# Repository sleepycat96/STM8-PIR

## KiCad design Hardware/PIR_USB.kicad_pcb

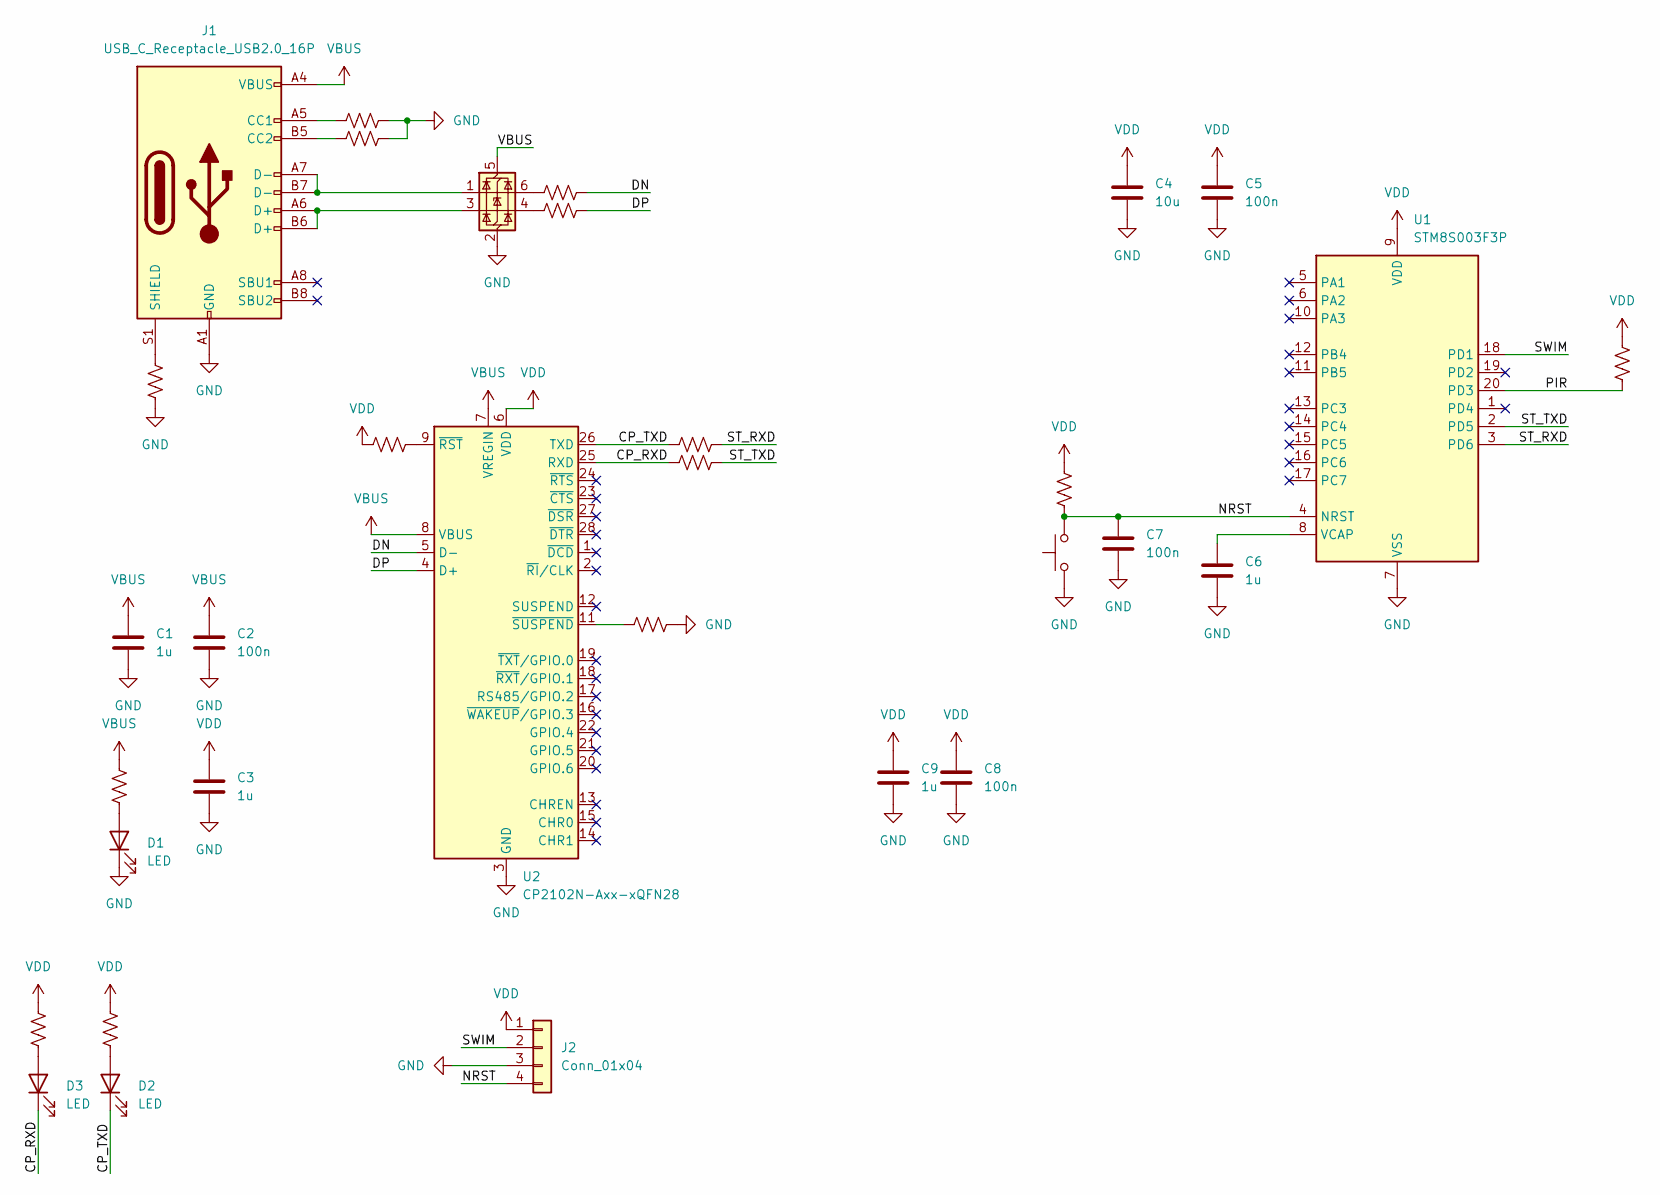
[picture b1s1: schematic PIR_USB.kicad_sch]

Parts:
C1, C3, C6, C9: 1u; C_0603_1608Metric
C2, C5, C7, C8: 100n; C_0603_1608Metric
C4: 10u; CP_EIA-3216-10_Kemet-I
D1, D2, D3: LED; LED_0603_1608Metric
J1: USB_C_Receptacle_USB2.0_16P; USB_C_Receptacle_GCT_USB4105-xx-A_16P_TopMnt_Horizontal
J2: Conn_01x04
R1, R2: 5.1k; R_0603_1608Metric
R3, R4, R7, R8: 22R; R_0603_1608Metric
R5, R9, R10, R11, R12, R13, R14: 10k; R_0603_1608Metric
R6: 0R; R_0603_1608Metric
SW1: SW_Push
U1: STM8S003F3P; TSSOP-20_4.4x6.5mm_P0.65mm
U2: CP2102N-Axx-xQFN28; QFN-28-1EP_5x5mm_P0.5mm_EP3.35x3.35mm
U3: USBLC6-2SC6; SOT-23-6

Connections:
/CP_RXD: D3.1 (K), R8.1, U2.25 (RXD)
/CP_TXD: D2.1 (K), R7.1, U2.26 (TXD)
/DN: R3.2, U2.5 (D-)
/DP: R4.2, U2.4 (D+)
/NRST: C7.1, J2.4, R13.1, SW1.2, U1.4 (NRST)
/ONTIME: U1.1 (PD4); also elsewhere on the board
/PIR: R14.1, U1.20 (PD3); also elsewhere on the board
/ST_RXD: R7.2, U1.3 (PD6)
/ST_TXD: R8.2, U1.2 (PD5)
/SWIM: J2.2, U1.18 (PD1)
GND: C1.2, C2.2, C3.2, C4.2, C5.2, C6.2, C7.2, C8.2, C9.2, D1.1 (K), J1.A1 (GND), J1.A12 (GND), J1.B1 (GND), J1.B12 (GND), J1.S1 (SHIELD), J2.3, R1.2, R2.2, R6.1, R6.2, R9.2, SW1.1, U1.7 (VSS), U2.3 (GND), U2.29 (GND), U3.2 (GND); also elsewhere on the board
unnamed: D1.2 (A), R10.1
unnamed: D2.2 (A), R11.1
unnamed: D3.2 (A), R12.1
unnamed: J1.A5 (CC1), R2.1
unnamed: J1.B5 (CC2), R1.1
unnamed: J1.A6 (D+), J1.B6 (D+), U3.3 (I/O2)
unnamed: J1.A7 (D-), J1.B7 (D-), U3.1 (I/O1)
unnamed: R3.1, U3.6 (I/O1)
unnamed: R4.1, U3.4 (I/O2)
unnamed 21: U1.5 (PA1); also elsewhere on the board
unnamed: C6.1, U1.8 (VCAP)
unnamed: R5.2, U2.9 (~RST)
unnamed: R9.1, U2.11 (~SUSPEND)
VBUS: C1.1, C2.1, J1.A4 (VBUS), J1.A9 (VBUS), J1.B4 (VBUS), J1.B9 (VBUS), R10.2, U2.7 (VREGIN), U2.8 (VBUS), U3.5 (VBUS)

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
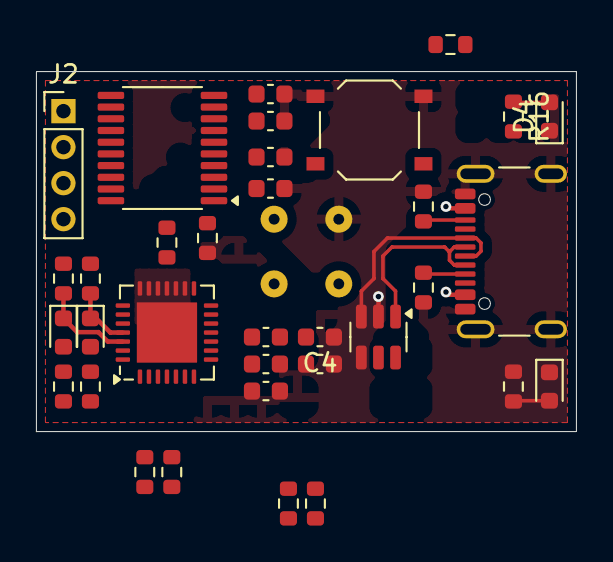
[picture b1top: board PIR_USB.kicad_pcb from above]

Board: 2 copper layers, 30.0 x 20.0 mm, 35 parts (1 on the bottom side), 27 nets.

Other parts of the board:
D4: LED; LED_0603_1608Metric
J3: BS412
R15, R16: 10k; R_0603_1608Metric

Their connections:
/ONTIME: J3.2, R15.1; also elsewhere on the board
/PIR: J3.4; also elsewhere on the board
GND: D4.1 (K), J3.1; also elsewhere on the board
unnamed: D4.2 (A), R16.1
unnamed 21: R16.2; also elsewhere on the board

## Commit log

2024-07-07 schematic 080724
2025-03-24 250325
2025-03-24 250325 2
2025-03-25 250325 3
